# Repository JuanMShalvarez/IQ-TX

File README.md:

This project serves to implement fully capable, relatively narrowband and low data rate software defined radio transmitter for amateurs.
Goal is to avoid use of FPGA at all costs and utilize analog peripherals of microcontrollers instead. 

Ideally, data input should be done via famous open source software like GNU Radio.

Responsibility of safe usage, including electrical safety, falls entirely on user. 
Same applies to compliance to regulations determined by respective governing bodies/agencies for wireless communications in your area. 
Please consult the band plan of the location where you intend to operate and limitations applying to transmit power.

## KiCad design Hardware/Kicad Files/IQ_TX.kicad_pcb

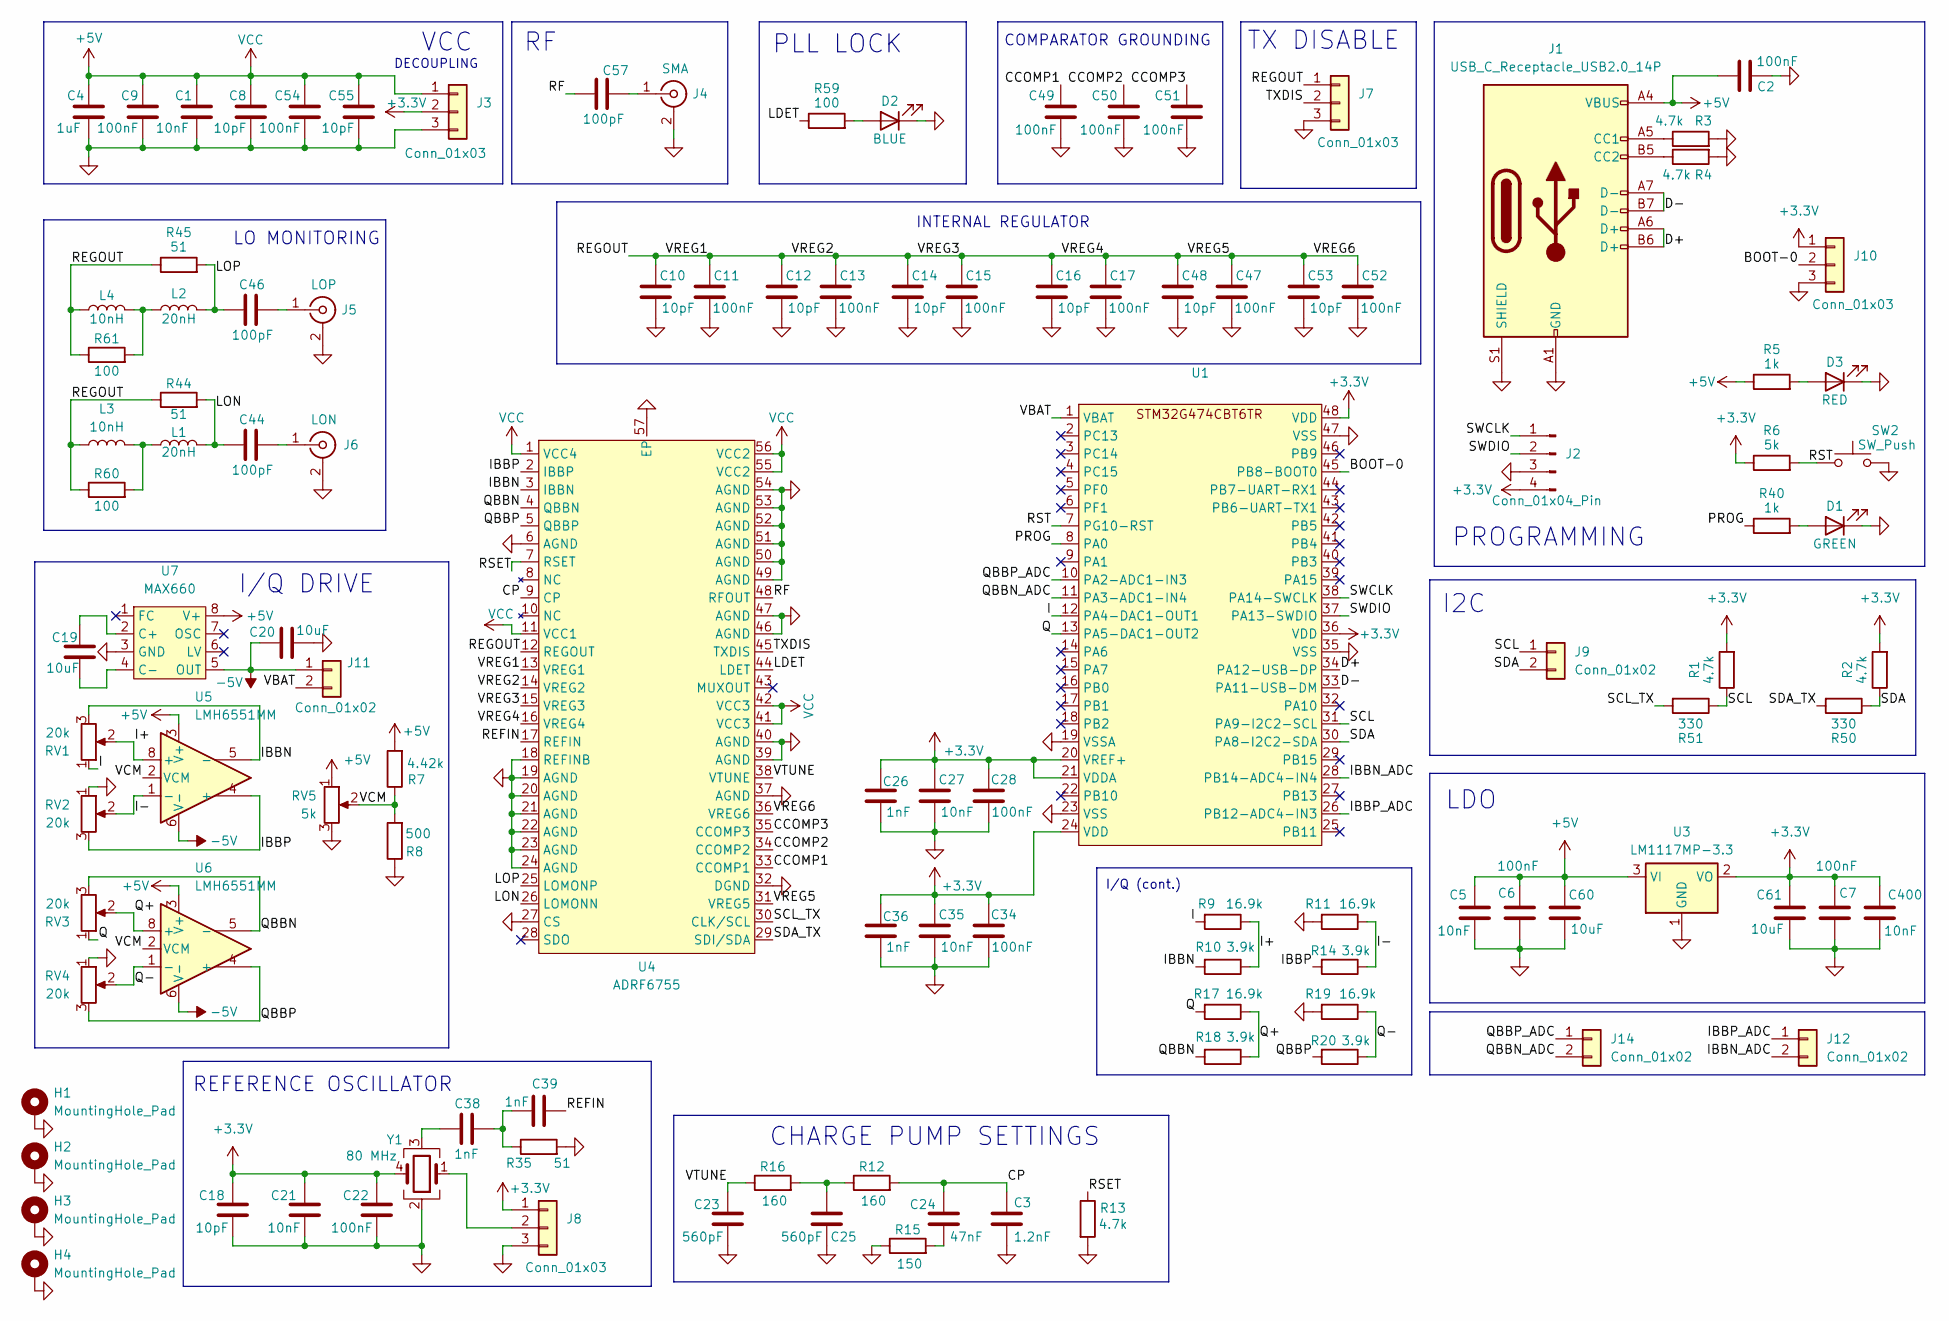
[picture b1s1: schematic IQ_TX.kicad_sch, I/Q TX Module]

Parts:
C1, C5, C21, C27, C35, C400: 10nF; C_0603_1608Metric
C2, C6, C7, C9, C11, C13, C15, C17, C22, C28, C34, C47, C49, C50, C51, C52, C54: 100nF; C_0603_1608Metric
C3: 1.2nF; C_0603_1608Metric
C4: 1uF; C_0603_1608Metric
C8, C10, C12, C14, C16, C18, C48, C53, C55: 10pF; C_0603_1608Metric
C19, C20: 10uF; C_0603_1608Metric
C23, C25: 560pF; C_0603_1608Metric
C24: 47nF; C_0603_1608Metric
C26, C36, C38, C39: 1nF; C_0603_1608Metric
C44, C46, C57: 100pF; C_0603_1608Metric
C60, C61: 10uF; CP_Elec_4x4.5
D1: GREEN; LED_0603_1608Metric
D2: BLUE; LED_0603_1608Metric
D3: RED; LED_0603_1608Metric
H1, H2, H3, H4: MountingHole_Pad; MountingHole_3.2mm_M3_Pad_Via
J1: USB_C_Receptacle_USB2.0_14P; USB_C_Receptacle_HRO_TYPE-C-31-M-12
J2: Conn_01x04_Pin; PinHeader_1x04_P2.54mm_Vertical
J3, J7, J8, J10: Conn_01x03; PinHeader_1x03_P2.54mm_Vertical
J4: SMA; SMA_Amphenol_901-144_Vertical
J5: LOP; SMA_Amphenol_901-144_Vertical
J6: LON; SMA_Amphenol_901-144_Vertical
J9, J11, J12, J14: Conn_01x02; PinHeader_1x02_P2.54mm_Vertical
L1, L2: 20nH; L_0603_1608Metric
L3, L4: 10nH; L_0603_1608Metric
R1, R2, R3, R4, R13: 4.7k; R_0603_1608Metric
R5, R40: 1k; R_0603_1608Metric
R6: 5k; R_0603_1608Metric
R7: 4.42k; R_0603_1608Metric
R8: 500; R_0603_1608Metric
R9, R11, R17, R19: 16.9k; R_0603_1608Metric
R10, R14, R18, R20: 3.9k; R_0603_1608Metric
R12, R16: 160; R_0603_1608Metric
R15: 150; R_0603_1608Metric
R35, R44, R45: 51; R_0603_1608Metric
R50, R51: 330; R_0603_1608Metric
R59, R60, R61: 100; R_0603_1608Metric
RV1, RV2, RV3, RV4: 20k; Potentiometer_Bourns_3386W_Horizontal
RV5: 5k; Potentiometer_Bourns_3386W_Horizontal
SW2: SW_Push; SW_Push_1P1T_XKB_TS-1187A
U1: LQFP-48_7x7mm_P0.5mm
U3: LM1117MP-3.3; SOT-223-3_TabPin2
U4: ADRF6755; LFCSP-56-1EP_8x8mm_P0.5mm_EP6.6x6.6mm
U5, U6: LMH6551MM; VSSOP-8_3x3mm_P0.65mm
U7: MAX660; SOP-8_3.76x4.96mm_P1.27mm
Y1: 80 MHz; Oscillator_SMD_EuroQuartz_XO32-4Pin_3.2x2.5mm

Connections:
+3.3V: C7.2, C18.2, C21.2, C22.2, C26.2, C27.2, C28.2, C34.2, C35.2, C36.2, C61.1, C400.2, J2.4, J3.2, J8.1, J10.1, R1.2, R2.2, R6.1, U1.20 (VREF+), U1.21 (VDDA), U1.24 (VDD), U1.36 (VDD), U1.48 (VDD), U3.2 (VO), Y1.4
+5V: C1.2, C2.2, C4.2, C5.2, C6.2, C8.2, C9.2, C54.2, C55.2, C60.1, J1.A4 (VBUS), J1.A9 (VBUS), J1.B4 (VBUS), J1.B9 (VBUS), J3.1, R5.1, R7.2, RV5.1, U3.3 (VI), U4.1 (VCC4), U4.11 (VCC1), U4.41 (VCC3), U4.42 (VCC3), U4.55 (VCC2), U4.56 (VCC2), U5.3 (V+), U6.3 (V+), U7.8 (V+)
-5V: C20.2, J11.1, U5.6 (V-), U6.6 (V-), U7.5 (OUT)
/BOOT-0: J10.2, U1.45 (PB8-BOOT0)
/CCOMP1: C49.2, U4.33 (CCOMP1)
/CCOMP2: C50.2, U4.34 (CCOMP2)
/CCOMP3: C51.2, U4.35 (CCOMP3)
/CP: C3.2, C24.2, R12.2, U4.9 (CP)
/D+: J1.A6 (D+), J1.B6 (D+), U1.34 (PA12-USB-DP)
/D-: J1.A7 (D-), J1.B7 (D-), U1.33 (PA11-USB-DM)
/I: R9.2, RV1.1, U1.12 (PA4-DAC1-OUT1)
/I+: R9.1, R10.1, RV1.2, U5.8 (+)
/I-: R11.1, R14.1, RV2.2, U5.1 (-)
/IBBN: R10.2, RV1.3, U4.3 (IBBN), U5.5 (-)
/IBBN_ADC: J12.2, U1.28 (PB14-ADC4-IN4)
/IBBP: R14.2, RV2.3, U4.2 (IBBP), U5.4 (+)
/IBBP_ADC: J12.1, U1.26 (PB12-ADC4-IN3)
/LDET: R59.1, U4.44 (LDET)
/LON: C44.1, L1.2, R44.2, U4.26 (LOMONN)
/LOP: C46.1, L2.2, R45.2, U4.25 (LOMONP)
/PROG: R40.1, U1.8 (PA0)
/Q: R17.2, RV3.1, U1.13 (PA5-DAC1-OUT2)
/Q+: R17.1, R18.1, RV3.2, U6.8 (+)
/Q-: R19.1, R20.1, RV4.2, U6.1 (-)
/QBBN: R18.2, RV3.3, U4.4 (QBBN), U6.5 (-)
/QBBN_ADC: J14.2, U1.11 (PA3-ADC1-IN4)
/QBBP: R20.2, RV4.3, U4.5 (QBBP), U6.4 (+)
/QBBP_ADC: J14.1, U1.10 (PA2-ADC1-IN3)
/REFIN: C39.1, U4.17 (REFIN)
/REGOUT: C10.2, C11.2, C12.2, C13.2, C14.2, C15.2, C16.2, C17.2, C47.2, C48.2, C52.2, C53.2, J7.1, L3.1, L4.1, R44.1, R45.1, R60.1, R61.1, U4.12 (REGOUT), U4.13 (VREG1), U4.14 (VREG2), U4.15 (VREG3), U4.16 (VREG4), U4.31 (VREG5), U4.36 (VREG6)
/RF: C57.1, U4.48 (RFOUT)
/RSET: R13.1, U4.7 (RSET)
/RST: R6.2, SW2.1, U1.7 (PG10-RST)
/SCL: J9.1, R1.1, R51.1, U1.31 (PA9-I2C2-SCL)
/SCL_TX: R51.2, U4.30 (CLK/SCL)
/SDA: J9.2, R2.1, R50.1, U1.30 (PA8-I2C2-SDA)
/SDA_TX: R50.2, U4.29 (SDI/SDA)
/SWCLK: J2.1, U1.38 (PA14-SWCLK)
/SWDIO: J2.2, U1.37 (PA13-SWDIO)
/TXDIS: J7.2, U4.45 (TXDIS)
/VBAT: J11.2, U1.1 (VBAT)
/VCM: R7.1, R8.2, RV5.2, U5.2 (VCM), U6.2 (VCM)
/VTUNE: C23.2, R16.1, U4.38 (VTUNE)
GND: C1.1, C2.1, C3.1, C4.1, C5.1, C6.1, C7.1, C8.1, C9.1, C10.1, C11.1, C12.1, C13.1, C14.1, C15.1, C16.1, C17.1, C18.1, C20.1, C21.1, C22.1, C23.1, C25.1, C26.1, C27.1, C28.1, C34.1, C35.1, C36.1, C47.1, C48.1, C49.1, C50.1, C51.1, C52.1, C53.1, C54.1, C55.1, C60.2, C61.2, C400.1, D1.1 (K), D2.1 (K), D3.1 (K), H1.1, H2.1, H3.1, H4.1, J1.A1 (GND), J1.A12 (GND), J1.B1 (GND), J1.B12 (GND), J1.S1 (SHIELD), J2.3, J3.3, J4.2 (Ext), J5.2 (Ext), J6.2 (Ext), J7.3, J8.3, J10.3, R3.2, R4.2, R8.1, R11.2, R13.2, R15.1, R19.2, R35.2, RV2.1, RV4.1, RV5.3, SW2.2, U1.19 (VSSA), U1.23 (VSS), U1.35 (VSS), U1.47 (VSS), U3.1 (GND), U4.6 (AGND), U4.18 (REFINB), U4.19 (AGND), U4.20 (AGND), U4.21 (AGND), U4.22 (AGND), U4.23 (AGND), U4.24 (AGND), U4.27 (CS), U4.32 (DGND), U4.37 (AGND), U4.39 (AGND), U4.40 (AGND), U4.46 (AGND), U4.47 (AGND), U4.49 (AGND), U4.50 (AGND), U4.51 (AGND), U4.52 (AGND), U4.53 (AGND), U4.54 (AGND), U4.57 (EP), U7.3 (GND), Y1.2
unnamed: C24.1, R15.2
unnamed: C25.2, R12.1, R16.2
unnamed: C38.1, C39.2, R35.1
unnamed: C38.2, Y1.3
unnamed: D1.2 (A), R40.2
unnamed: D2.2 (A), R59.2
unnamed: D3.2 (A), R5.2
unnamed: J1.A5 (CC1), R3.1
unnamed: J1.B5 (CC2), R4.1
unnamed: C57.2, J4.1 (In)
unnamed: C46.2, J5.1 (In)
unnamed: C44.2, J6.1 (In)
unnamed: J8.2, Y1.1
unnamed: L1.1, L3.2, R60.2
unnamed: L2.1, L4.2, R61.2
unnamed: C19.2, U7.2 (C+)
unnamed: C19.1, U7.4 (C-)

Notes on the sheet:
DECOUPLING
I/Q (cont.)
TX DISABLE
COMPARATOR GROUNDING
I/Q DRIVE
I2C
REFERENCE OSCILLATOR
PROGRAMMING
VCC
INTERNAL REGULATOR
PLL LOCK
CHARGE PUMP SETTINGS
LO MONITORING
LDO

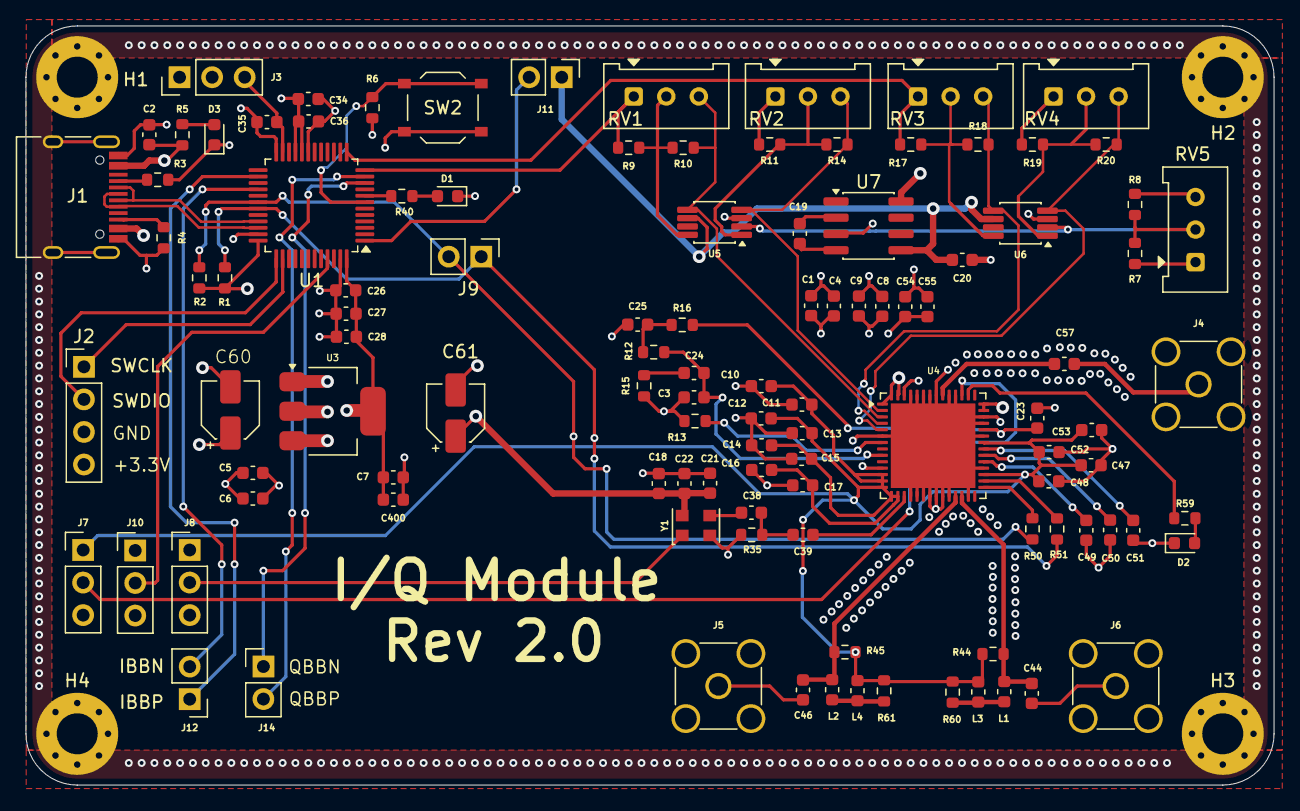
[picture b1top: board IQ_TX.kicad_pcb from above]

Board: 4 copper layers, 97.4 x 59.2 mm, 114 parts (0 on the bottom side), 61 nets.

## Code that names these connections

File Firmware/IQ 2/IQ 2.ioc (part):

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Mcu.Name=STM32G474C(B-C-E)Tx
Mcu.Package=LQFP48
Mcu.UserName=STM32G474CBTx
PA0.Signal=GPIO_Output
PA11.Mode=Device
PA11.Signal=USB_DM
PA12.Mode=Device
PA12.Signal=USB_DP
PA4.Signal=COMP_DAC11_group
PA5.Signal=COMP_DAC12_group
PA8.Mode=I2C
PA8.Signal=I2C2_SDA
PA9.Mode=I2C
PA9.Signal=I2C2_SCL
RCC.HSE_VALUE=8000000
RCC.SYSCLKFreq_VALUE=160000000
RCC.SYSCLKSource=RCC_SYSCLKSOURCE_PLLCLK
board=custom
